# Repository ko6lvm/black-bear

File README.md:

# black bear
black bear is an ESP32-based CAN scanner for your car. 

<image src="img/blender/front.png" width=500>

### Purpose
black bear is for diagnosing and pulling information from any car, such as information and faults about the powertrain, steering rack, and more. It is too complicated to get into on a README like this; more information can be found on pages like [OBDSolutions](https://www.obdsol.com/knowledgebase/on-board-diagnostics/what-data-is-available-from-obd/), [SAE J1979](https://legacy.sae.org/standards/), and the [OBD-II PIDs Wikipedia page](https://en.wikipedia.org/wiki/OBD-II_PIDs).  

### Connection
black bear connects to your car's OBD-II port found on every passenger vehicle made after 1996 in the United States. More about OBD-II can be found [here](https://en.wikipedia.org/wiki/On-board_diagnostics#:~:text=OBD%2DIIedit).

## PCB
### Specs
The PCB is designed with JLCPCB standards in mind:
* 2-layer PCB, 1.6mm, FR4, Green
* OSP, HASL, or ENIG coating

Additionally, assembly can be done by JLCPCB PCBA, with the following constraints:
* ESP32 assembly requires Standard PCBA, and not Economic PCBA
* OBD-II port (THT) is not readily available on LCSC/JLCPCB Parts, so you'll have to do that yourself.

### Files

* CPL/BOM files for JLCPCB PCBA is under `pcb/`, marked `_eco.csv` for economic PCBA and `_standard.csv` for standard PCBA.
* Gerber ZIP for both Economic and Standard is at `pcb/black-bear-rev-1.2.zip`.
* KiCAD 10 project files are at `pcb/`, as `bear.kicad_pcb`, `bear.kicad_prl`, `bear.kicad_pro`, and `bear.kicad_sch`.
* KiCAD 10 library files are at `pcb/lib/`.

### Images
<details>
<summary>KiCAD PCB 3D View (collapsable as image is large)</summary>
<image src="img/pcb.png" width=500>
</details>

<details>
<summary>KiCAD PCB Editor View (collapsable as image is large)</summary>
<image src="img/pcb-editor.png" width=700>
</details>

## Schematic
### Images
<details>
<summary>Full Schematic (collapsable as image is large)</summary>
<image src="img/schematic.png" width=700>
</details>

## Case
### Specs
Only use PETG, ABS, or ASA. PLA will deform in a hot car.  
M3 screws are to be used. There are two options of the top case tray, one for self-tap M3 screws, and one for M3 screws with heatset inserts.
### Images
<details>
<summary>Renders (collapsable as image is large)</summary>
<image src="img/blender/front.png" width=700>
<image src="img/blender/bottom.png" width=700>
<image src="img/blender/macro.png" width=700>
<image src="img/blender/exploded.png" width=700>
<image src="img/blender/open.png" width=700>
</details>

<details>
<summary>Case Trays (collapsable as image is large)</summary>
<image src="img/top-heatset.png" width=700>
<image src="img/bottom.png" width=700>
</details>

## Firmware
black bear is not supplied with firmware made specifically for black bear, as there are open-source options that are community-tested and support multiple apps/host software.  [meatpiHQ/wican-fw](https://github.com/meatpihq/wican-fw) is recommended; it supports `elm327` (required for black bear's CAN setup) as well as `slcand` and `gvret` for the host software.

### wican-fw setup
```bash
bash ./fw/edit-wican.sh
cd fw/wican-fw

# Only needed on the very first build
idf.py set-target esp32s3

idf.py -p /dev/ttyACM0 build flash
```

## BoM
Also available at `bom.csv` (csv contains costs). Costs may vary.

| Designator | Qty | Value | Description | Package | Manufacturer | MPN | Link |
| :--- | :---: | :--- | :--- | :--- | :--- | :--- | :--- |
| `U1` | 1 | `ESP32-S3-WROOM-1-N8` | ESP32-S3 Wi-Fi + BLE MCU (8MB Flash) | Module | Espressif Systems | `ESP32-S3-WROOM-1-N8` | [C2913198](https://jlcpcb.com/partdetail/C2913198) |
| `U2` | 1 | `SN65HVD230` | 3.3V CAN Transceiver (1 Mbps) | SOIC-8 | Texas Instruments | `SN65HVD230DR` | [C12084](https://jlcpcb.com/partdetail/C12084) |
| `U3` | 1 | `AP2112K-3.3` | 3.3V 600mA LDO Regulator | SOT-23-5 | Diodes Incorporated | `AP2112K-3.3TRG1` | [C51118](https://jlcpcb.com/partdetail/C51118) |
| `U4` | 1 | `AP63205WU` | 3.8-32V to 5V 2A Buck Converter | TSOT-23-6 | Diodes Incorporated | `AP63205WU-7` | [C2071056](https://jlcpcb.com/partdetail/C2071056) |
| `D1` | 1 | `NUP2105L` | Dual 24V CAN ESD/TVS Diode | SOT-23 | onsemi | `NUP2105LT1G` | [C14486](https://jlcpcb.com/partdetail/C14486) |
| `D2, D3, D4` | 3 | `1N5819WS` | 40V 1A Schottky Diode | SOD-323 | Guangdong Hottech | `1N5819WS` | [C191023](https://jlcpcb.com/partdetail/C191023) |
| `D5` | 1 | `SMBJ18A` | 18V 600W Unidirectional TVS Diode | SMB | MDD | `SMBJ18A` | [C353379](https://jlcpcb.com/partdetail/C353379) |
| `F1` | 1 | `500mA` | 30V 500mA Resettable PTC Fuse | 1812 | Jinrui | `JK-MSMD050-30` | [C369168](https://jlcpcb.com/partdetail/C369168) |
| `L1` | 1 | `4.7uH` | 4.7uH 6A Shielded Power Inductor | 7.3x6.6mm | Sunlord | `MWSA0603S-4R7MT` | [C408447](https://jlcpcb.com/partdetail/C408447) |
| `J1` | 1 | `CCBDM20` | OBD-II 16-Pin Male Right-Angle (Hand-Solder) | THT | Generic | `CCBDM20` | [eBay](https://www.ebay.com/itm/307150583236) |
| `J2` | 1 | `TYPE-C-31-M-12` | USB 2.0 Type-C Receptacle (16P) | SMD+THT | Korean Hroparts Elec | `TYPE-C-31-M-12` | [C165948](https://jlcpcb.com/partdetail/C165948) |
| `SW1, SW2` | 2 | `GT-TZ084B-H015-L1` | Tactile Pushbutton Switch (BOOT / RESET) | 5.2x5.2mm | G-Switch | `GT-TZ084B-H015-L1` | [C29780122](https://jlcpcb.com/partdetail/C29780122) |
| `R1` | 1 | `100R` | 100 Ohm 1% Resistor | 0603 | UNI-ROYAL | `0603WAF1000T5E` | [C22775](https://jlcpcb.com/partdetail/C22775) |
| `R2, R3` | 2 | `0R` | 0 Ohm Jumper | 0603 | UNI-ROYAL | `0603WAF0000T5E` | [C21189](https://jlcpcb.com/partdetail/C21189) |
| `R4, R9` | 2 | `10k` | 10 kOhm 1% Resistor | 0603 | UNI-ROYAL | `0603WAF1002T5E` | [C25804](https://jlcpcb.com/partdetail/C25804) |
| `R5, R6` | 2 | `5.1k` | 5.1 kOhm 1% Resistor | 0603 | UNI-ROYAL | `0603WAF5101T5E` | [C23186](https://jlcpcb.com/partdetail/C23186) |
| `R7` | 1 | `100k` | 100 kOhm 1% Resistor | 0603 | UNI-ROYAL | `0603WAF1003T5E` | [C25803](https://jlcpcb.com/partdetail/C25803) |
| `R8` | 1 | `16k` | 16 kOhm 1% Resistor | 0603 | UNI-ROYAL | `0603WAF1602T5E` | [C4210](https://jlcpcb.com/partdetail/C4210) |
| `C4, C9, C10, C13, C14, C15, C17` | 7 | `100nF` | 100nF 50V X7R Capacitor | 0603 | Yageo | `CC0603KRX7R9BB104` | [C14663](https://jlcpcb.com/partdetail/C14663) |
| `C5` | 1 | `1uF` | 1uF 50V X5R Capacitor | 0603 | Samsung Electro-Mechanics | `CL10A105KB8NNNC` | [C15849](https://jlcpcb.com/partdetail/C15849) |
| `C6, C7, C16` | 3 | `10uF` | 10uF 25V X5R Capacitor | 0805 | Samsung Electro-Mechanics | `CL21A106KAYNNNE` | [C15850](https://jlcpcb.com/partdetail/C15850) |
| `C8` | 1 | `10uF` | 10uF 50V X5R Capacitor | 1206 | Samsung Electro-Mechanics | `CL31A106KBHNNNE` | [C13585](https://jlcpcb.com/partdetail/C13585) |
| `C11, C12` | 2 | `22uF` | 22uF 16V X5R Capacitor | 0805 | Samsung Electro-Mechanics | `CL21A226MOQNNNE` | [C98190](https://jlcpcb.com/partdetail/C98190) |

Note: `J1` (the OBD-II port) is not usually available from Macchina, so an alternative from other sites such as [this one from eBay](https://www.ebay.com/itm/307150583236) for ~$15 will work as well.

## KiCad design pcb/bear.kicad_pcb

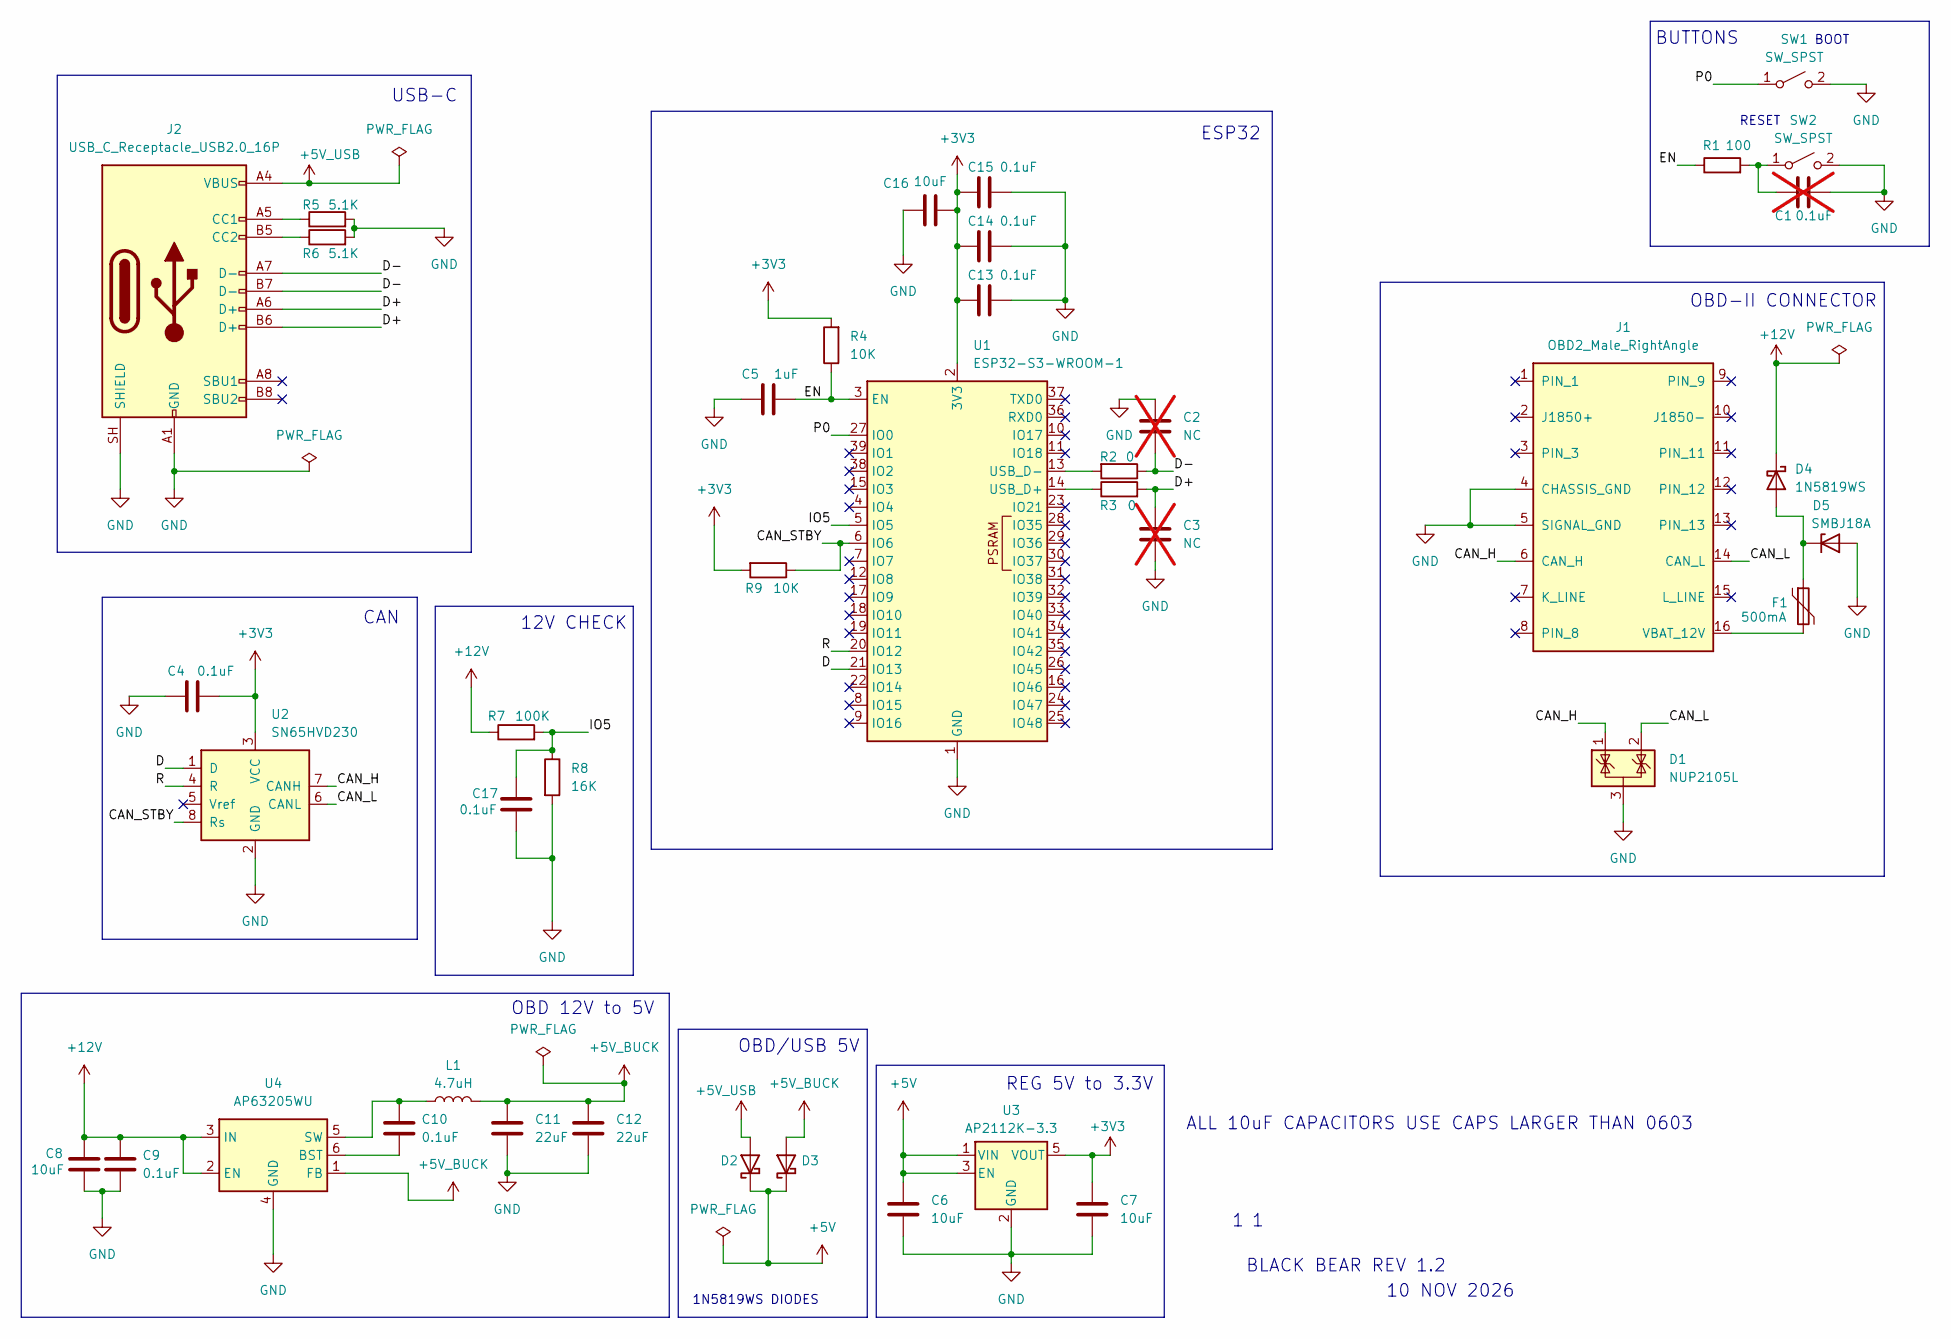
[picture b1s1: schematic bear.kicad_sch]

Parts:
C1: 0.1uF; C_0603_1608Metric; not fitted
C2, C3: NC; C_0603_1608Metric; not fitted
C4, C9, C10, C13, C14, C15, C17: 0.1uF; C_0603_1608Metric
C5: 1uF; C_0603_1608Metric
C6, C7, C16: 10uF; C_0805_2012Metric
C8: 10uF; C_1206_3216Metric
C11, C12: 22uF; C_0805_2012Metric
D1: NUP2105L; SOT-23
D2, D3, D4: 1N5819WS; D_SOD-323
D5: SMBJ18A; D_SMB
F1: 500mA; Fuse_1812_4532Metric
J1: OBD2_Male_RightAngle
J2: USB_C_Receptacle_USB2.0_16P; USB_C_Receptacle_HRO_TYPE-C-31-M-12
L1: 4.7uH; L_CKST0605
R1: 100; R_0603_1608Metric
R2, R3: 0; R_0603_1608Metric
R4, R9: 10K; R_0603_1608Metric
R5, R6: 5.1K; R_0603_1608Metric
R7: 100K; R_0603_1608Metric
R8: 16K; R_0603_1608Metric
SW1, SW2: SW_SPST; SW_SPST_TL3342
U1: ESP32-S3-WROOM-1
U2: SN65HVD230; SOIC-8_3.9x4.9mm_P1.27mm
U3: AP2112K-3.3; SOT-23-5
U4: AP63205WU; TSOT-23-6

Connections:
+3V3: C4.2, C7.1, C13.1, C14.1, C15.1, C16.2, R4.2, R9.2, U1.2 (3V3), U2.3 (VCC), U3.5 (VOUT)
+5V: C6.1, D2.1 (K), D3.1 (K), U3.1 (VIN), U3.3 (EN)
+5V_BUCK: C11.1, C12.1, D3.2 (A), L1.2, U4.1 (FB)
+5V_USB: D2.2 (A), J2.A4 (VBUS), J2.A9 (VBUS), J2.B4 (VBUS), J2.B9 (VBUS)
+12V: C8.1, C9.1, D4.1 (K), R7.1, U4.2 (EN), U4.3 (IN)
/CAN_H: D1.1 (K), J1.6 (CAN_H), U2.7 (CANH)
/CAN_L: D1.2 (K), J1.14 (CAN_L), U2.6 (CANL)
/CAN_STBY: R9.1, U1.6 (IO6), U2.8 (Rs)
/D: U1.21 (IO13), U2.1 (D)
/D+: C3.1, J2.A6 (D+), J2.B6 (D+), R3.2
/D-: C2.2, J2.A7 (D-), J2.B7 (D-), R2.1
/EN: C5.2, R1.1, R4.1, U1.3 (EN)
/IO5: C17.1, R7.2, R8.1, U1.5 (IO5)
/P0: SW1.1 (A), U1.27 (IO0)
/R: U1.20 (IO12), U2.4 (R)
GND: C1.2, C2.1, C3.2, C4.1, C5.1, C6.2, C7.2, C8.2, C9.2, C11.2, C12.2, C13.2, C14.2, C15.2, C16.1, C17.2, D1.3 (A), D5.2 (A), J1.4 (CHASSIS_GND), J1.5 (SIGNAL_GND), J2.A1 (GND), J2.A12 (GND), J2.B1 (GND), J2.B12 (GND), J2.SH (SHIELD), R5.2, R6.2, R8.2, SW1.2 (B), SW2.2 (B), U1.1 (GND), U1.40 (GND), U1.41 (GND), U2.2 (GND), U3.2 (GND), U4.4 (GND)
unnamed: D4.2 (A), D5.1 (K), F1.1
unnamed: F1.2, J1.16 (VBAT_12V)
unnamed: J2.A5 (CC1), R5.1
unnamed: J2.B5 (CC2), R6.1
unnamed: C1.1, R1.2, SW2.1 (A)
unnamed: R3.1, U1.14 (USB_D+)
unnamed: R2.2, U1.13 (USB_D-)
unnamed: C10.2, U4.6 (BST)
unnamed: C10.1, L1.1, U4.5 (SW)

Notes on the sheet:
USB-C
ESP32
CAN
10 NOV 2026
ALL 10uF CAPACITORS USE CAPS LARGER THAN 0603
REG 5V to 3.3V
OBD 12V to 5V
OBD/USB 5V
OBD-II CONNECTOR
12V CHECK
BOOT
RESET
BLACK BEAR REV 1.2
BUTTONS
1N5819WS DIODES

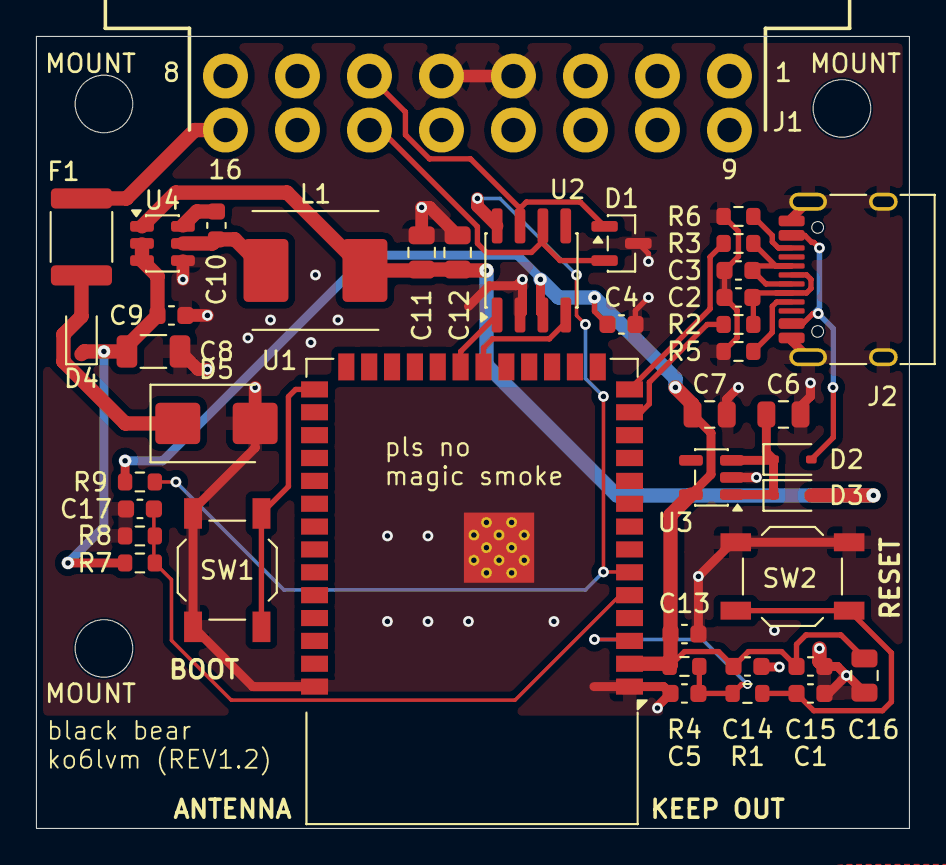
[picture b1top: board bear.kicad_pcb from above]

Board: 2 copper layers, 48.5 x 44.0 mm, 44 parts (0 on the bottom side), 25 nets.

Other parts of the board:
MOUNT: MountingHole_3.2mm_M3
MOUNT#2, MOUNT#3: MountingHole_3.2mm_M3

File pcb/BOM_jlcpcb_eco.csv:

Comment,Designator,Footprint,LCSC Part #
100,R1,R_0603_1608Metric,C22775
0,"R2,R3",R_0603_1608Metric,C21189
10K,"R4,R9",R_0603_1608Metric,C25804
5.1K,"R5,R6",R_0603_1608Metric,C23186
100K,R7,R_0603_1608Metric,C25803
16K,R8,R_0603_1608Metric,C4210
0.1uF,"C4,C9,C10,C13,C14,C15,C17",C_0603_1608Metric,C14663
1uF,C5,C_0603_1608Metric,C15849
10uF,"C6,C7,C16",C_0805_2012Metric,C15850
10uF,C8,C_1206_3216Metric,C13585
22uF,"C11,C12",C_0805_2012Metric,C98190
NUP2105L,D1,SOT-23,C14486
1N5819WS,"D2,D3,D4",D_SOD-323,C191023
SMBJ18A,D5,D_SMB,C353379
500mA,F1,Fuse_1812_4532Metric,C369168
4.7uH,L1,L_CKST0605,C408447
SW_SPST,"SW1,SW2",SW_SPST_TL3342,C29780122
SN65HVD230,U2,SOIC-8_3.9x4.9mm_P1.27mm,C12084
AP2112K-3.3,U3,SOT-23-5,C51118
AP63205WU,U4,TSOT-23-6,C2071056
USB_C_Receptacle_USB2.0_16P,J2,USB_C_Receptacle_HRO_TYPE-C-31-M-12,C165948
